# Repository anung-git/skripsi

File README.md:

# skripsi
skripsi pompa air iot

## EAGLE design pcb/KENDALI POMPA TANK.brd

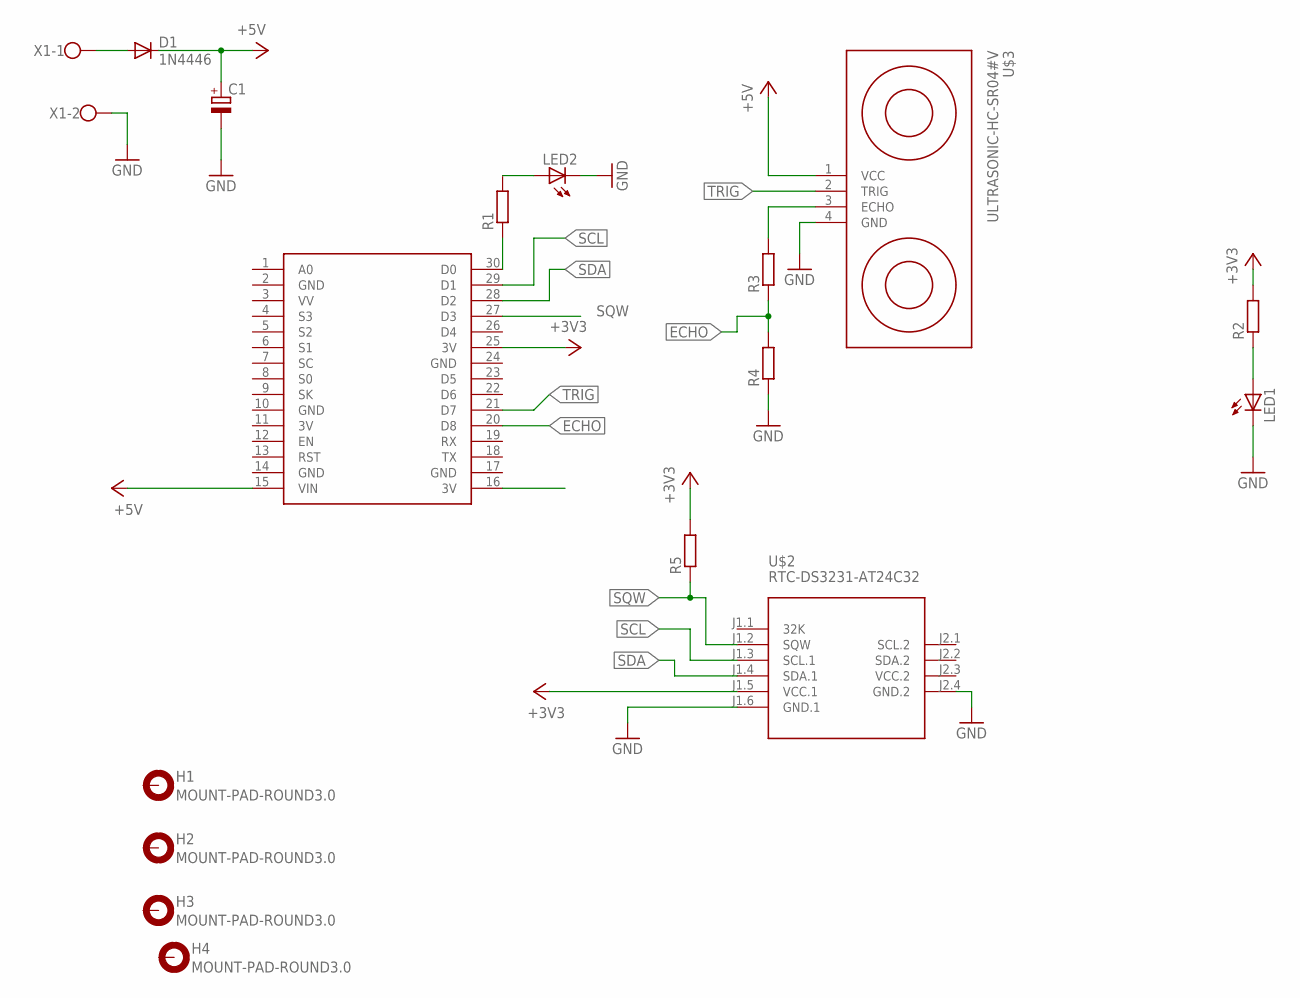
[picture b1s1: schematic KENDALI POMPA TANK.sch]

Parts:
C1: CPOL-EUE5-5; E5-5
D1: 1N4446; DO35-10
H1, H2, H3, H4: MOUNT-PAD-ROUND3.0; 3,0-PAD
LED1, LED2: LED5MM
R1, R2, R3, R4, R5: R-EU_0207/10; 0207/10
U$1: NODEMCU
U$2: RTC-DS3231-AT24C32
U$3: ULTRASONIC-HC-SR04#V
X1: W237-102

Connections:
3V: U$1.11 (3V)
+3V3: R2.2, R5.2, U$1.25 (3V), U$2.J1.5 (VCC.1)
+5V: C1.+, D1.C, U$1.15 (VIN), U$3.1 (VCC)
ECHO: R3.1, R4.2, U$1.20 (D8)
GND: C1.-, LED1.K (C), LED2.K (C), R4.1, U$1.2 (GND), U$1.10 (GND), U$1.14 (GND), U$1.17 (GND), U$1.24 (GND), U$2.J1.6 (GND.1), U$2.J2.4 (GND.2), U$3.4 (GND), X1.2
unnamed: R1.1, U$1.30 (D0)
unnamed: LED2.A, R1.2
unnamed: LED1.A, R2.1
unnamed: D1.A, X1.1
unnamed: R3.2, U$3.3 (ECHO)
SCL: U$1.29 (D1), U$2.J1.3 (SCL.1)
SDA: U$1.28 (D2), U$2.J1.4 (SDA.1)
SQW: R5.1, U$1.27 (D3), U$2.J1.2 (SQW)
TRIG: U$1.21 (D7), U$3.2 (TRIG)
VCC.2: U$2.J2.3 (VCC.2)

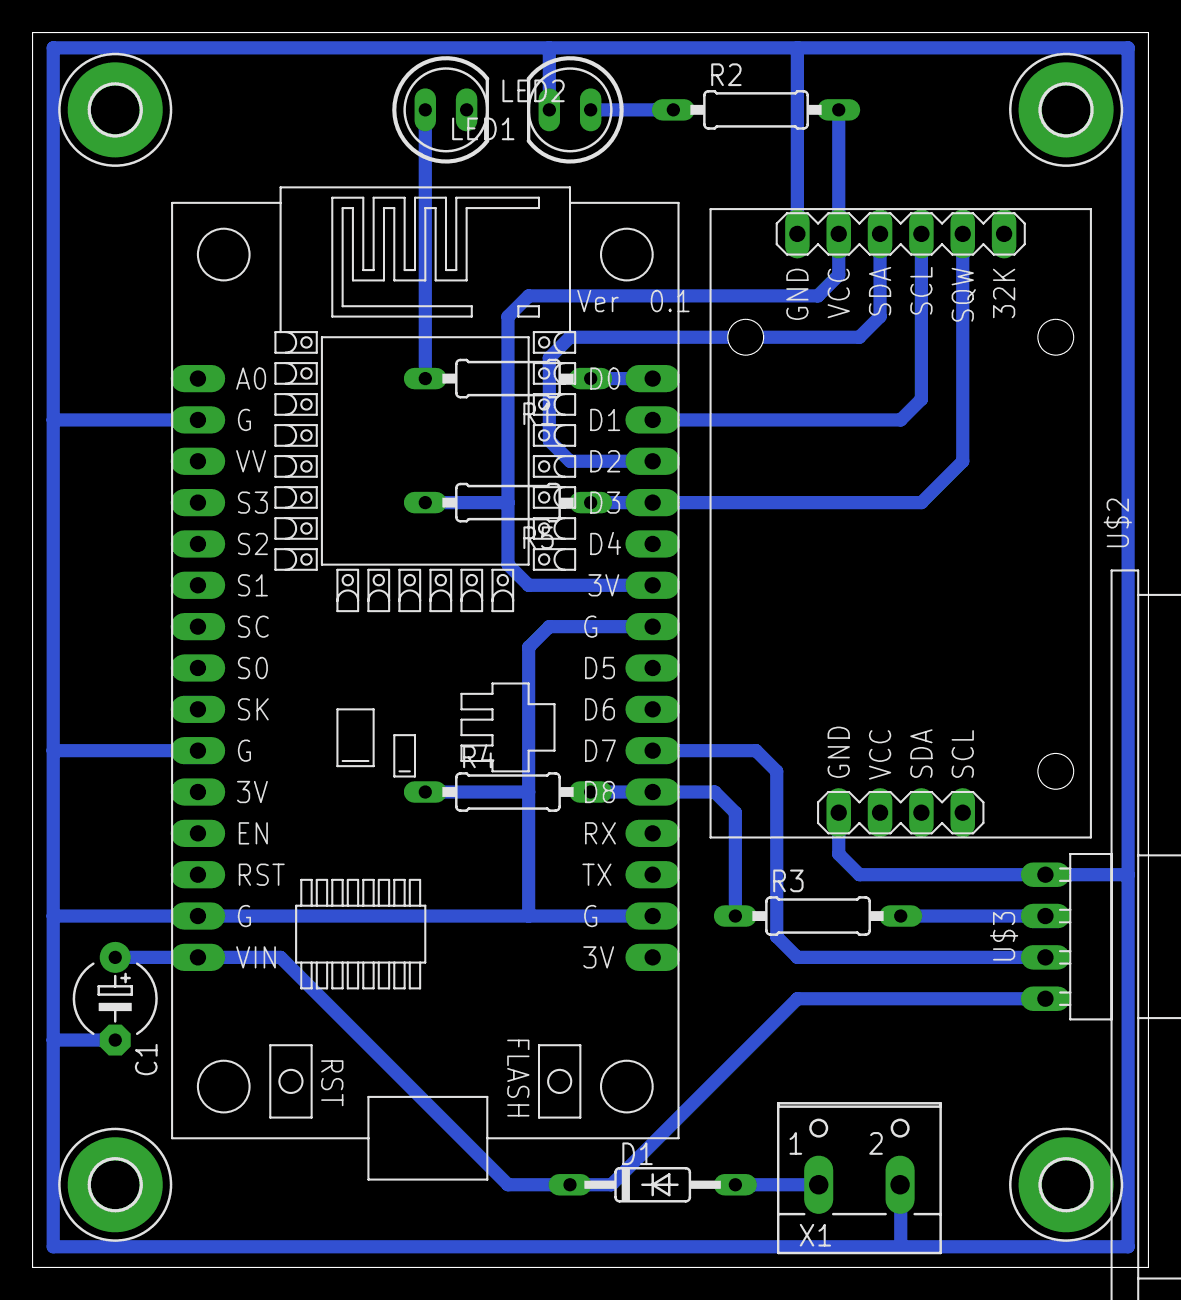
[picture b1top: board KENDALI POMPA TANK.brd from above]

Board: 2 copper layers, 68.6 x 75.9 mm, 17 parts (0 on the bottom side), 13 nets.

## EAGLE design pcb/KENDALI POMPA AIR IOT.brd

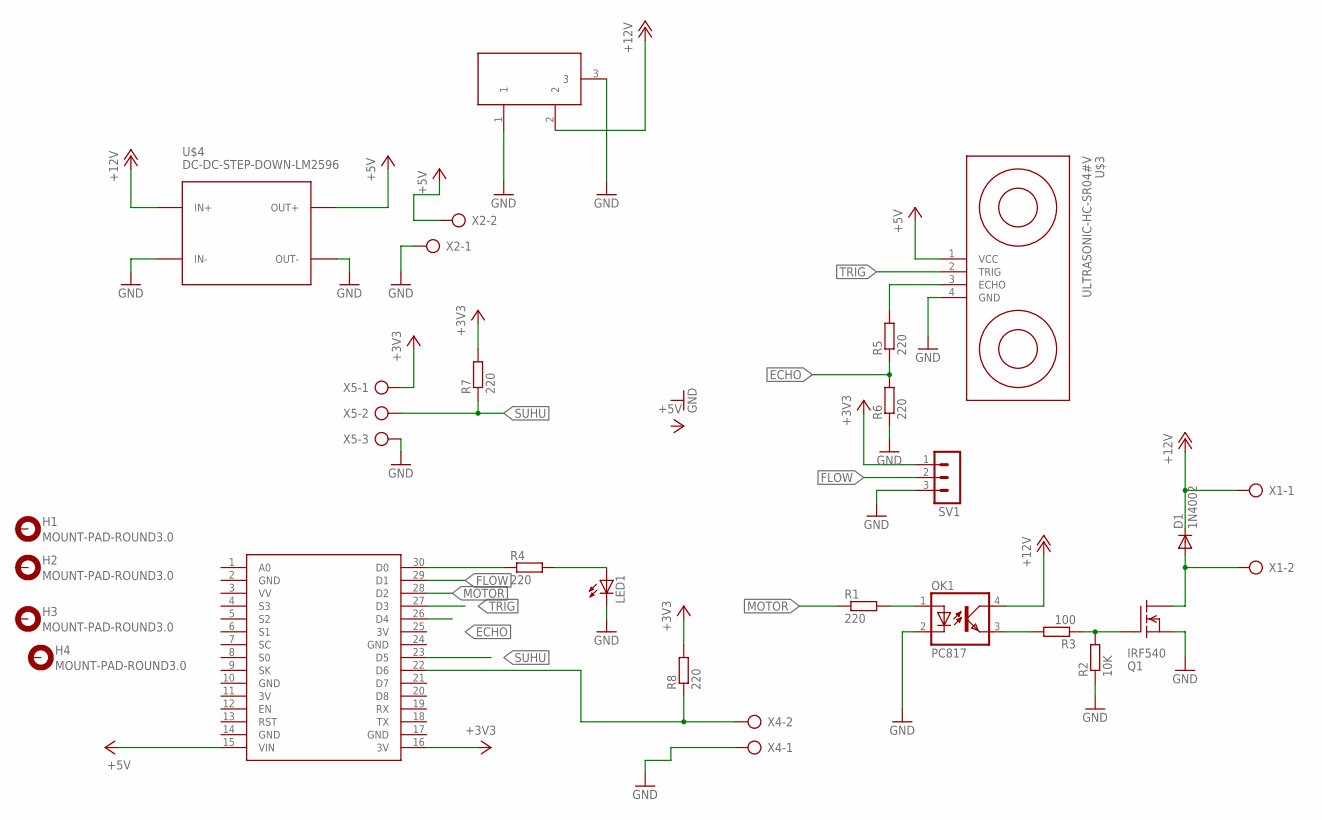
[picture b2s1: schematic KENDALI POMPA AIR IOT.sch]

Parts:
D1: 1N4002; DO35-10
H1, H2, H3, H4: MOUNT-PAD-ROUND3.0; 3,0-PAD
LED1: LED5MM
OK1: PC817; DIL04
Q1: IRF540; TO220
R1, R4, R5, R6, R7, R8: 220; 0207/10
R2: 10K; 0207/10
R3: 100; 0207/10
SV1: MA03-1
U$1: NODEMCU
U$2: DC21MMX; DC-21MM
U$3: ULTRASONIC-HC-SR04#V
U$4: DC-DC-STEP-DOWN-LM2596
X1, X2, X4: AK300/2
X5: AK300/3

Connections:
+3V3: R7.2, R8.2, SV1.1, U$1.11 (3V), U$1.16 (3V), U$1.25 (3V), X5.1
+5V: U$1.15 (VIN), U$3.1 (VCC), U$4.OUT+, X2.2
+12V: D1.C, OK1.4 (COL), U$2.2, U$4.IN+, X1.1
ECHO: R5.1, R6.2, U$1.26 (D4)
FLOW: SV1.2, U$1.29 (D1)
GND: LED1.K (C), OK1.2 (C), Q1.3 (S), R2.1, R6.1, SV1.3, U$1.2 (GND), U$1.10 (GND), U$1.14 (GND), U$1.17 (GND), U$1.24 (GND), U$2.1, U$2.3, U$3.4 (GND), U$4.IN-, U$4.OUT-, X2.1, X4.1, X5.3
MOTOR: R1.1, U$1.28 (D2)
unnamed: OK1.3 (EMIT), R3.2
unnamed: OK1.1 (A), R1.2
unnamed: Q1.1 (G), R2.2, R3.1
unnamed: D1.A, Q1.2 (D), X1.2
unnamed: LED1.A, R4.2
unnamed: R8.1, U$1.22 (D6), X4.2
unnamed: R4.1, U$1.30 (D0)
unnamed: R5.2, U$3.3 (ECHO)
SUHU: R7.1, U$1.23 (D5), X5.2
TRIG: U$1.27 (D3), U$3.2 (TRIG)

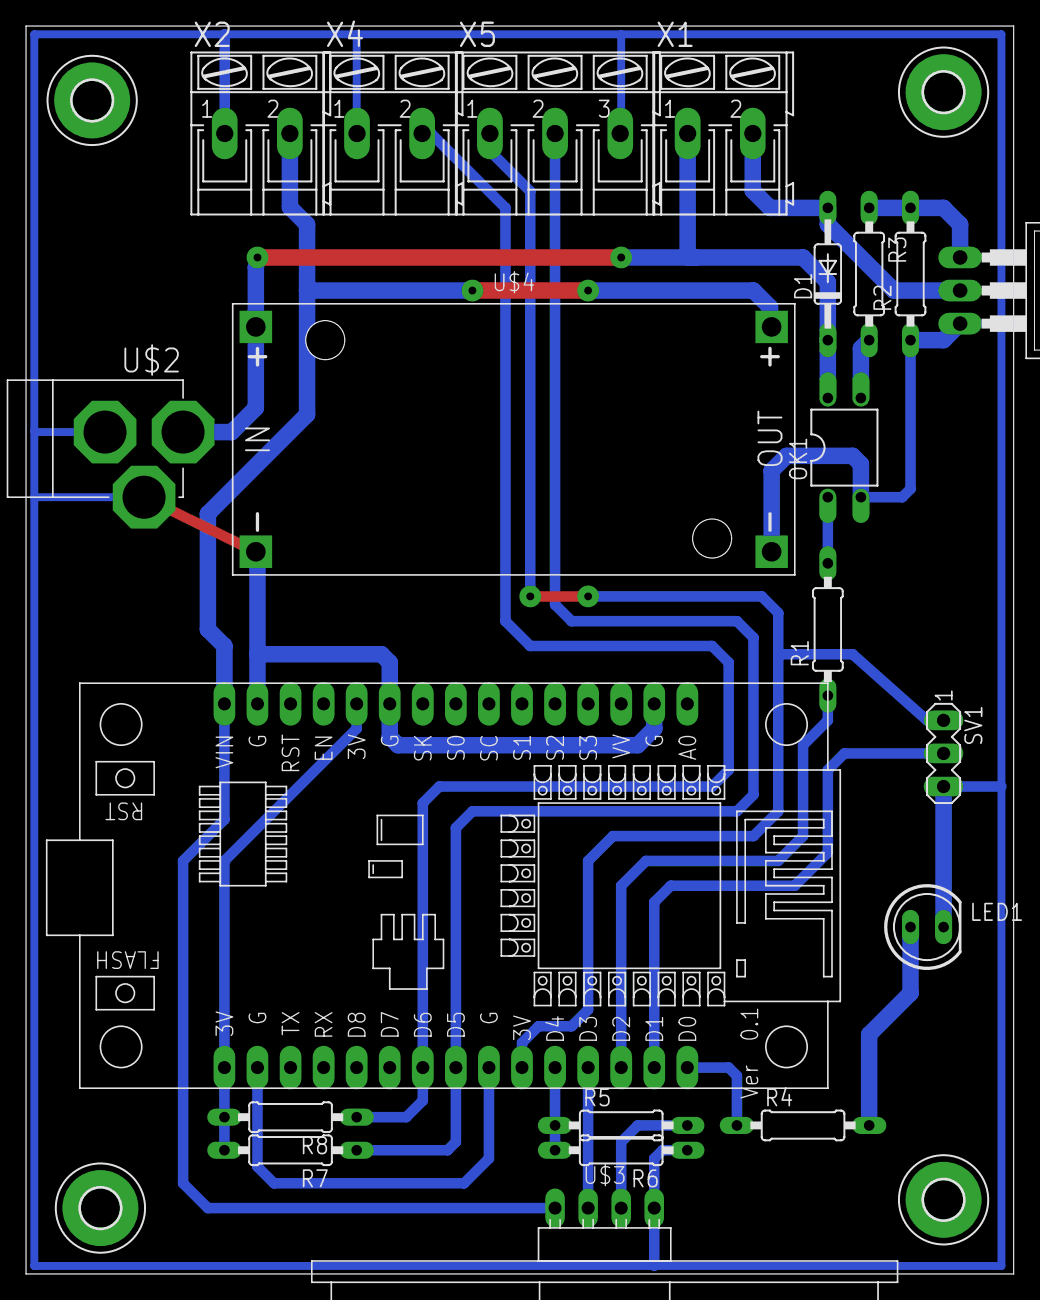
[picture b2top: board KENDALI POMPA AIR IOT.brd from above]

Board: 2 copper layers, 75.9 x 95.9 mm, 25 parts (0 on the bottom side), 17 nets.

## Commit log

2020-08-02 laporan
2020-08-02 revisi
2020-08-05 tambah software
2020-08-06 FLOWCHART
2020-08-10 revisi daya pompa
2020-08-13 yudisium
2020-08-16 lampiran
2020-08-17 jurnal

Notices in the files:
parts and their libraries:
diy-modules: Released under the Creative Commons Attribution 4.0 International License: http://creativecommons.org/licenses/by/4.0
SparkFun-Aesthetics: Licensing: Creative Commons ShareAlike 4.0 International - https://creativecommons.org/licenses/by-sa/4.0
